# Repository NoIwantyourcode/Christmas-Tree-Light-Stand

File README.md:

# Christmas-Tree-Light-Stand
This a christmas tree light stand that I made as a part of hackclub blueprint
and yes to any reviewer wondering, I am aiming for that shiny new Bambu labs A1 mini

Below are some pictures of the PCB, Rendered PCB, case, Schematics and a fully assembled view

# Schematics

# PCB
The Christmas tree lightstand uses 2 PCBs, The Christmas tree shaped PCB contains all the LEDs and the smaller but also important pcb as it handles the timing of the flashing LEDs and power

# Rendered PCB

# Case

# fully assembled view

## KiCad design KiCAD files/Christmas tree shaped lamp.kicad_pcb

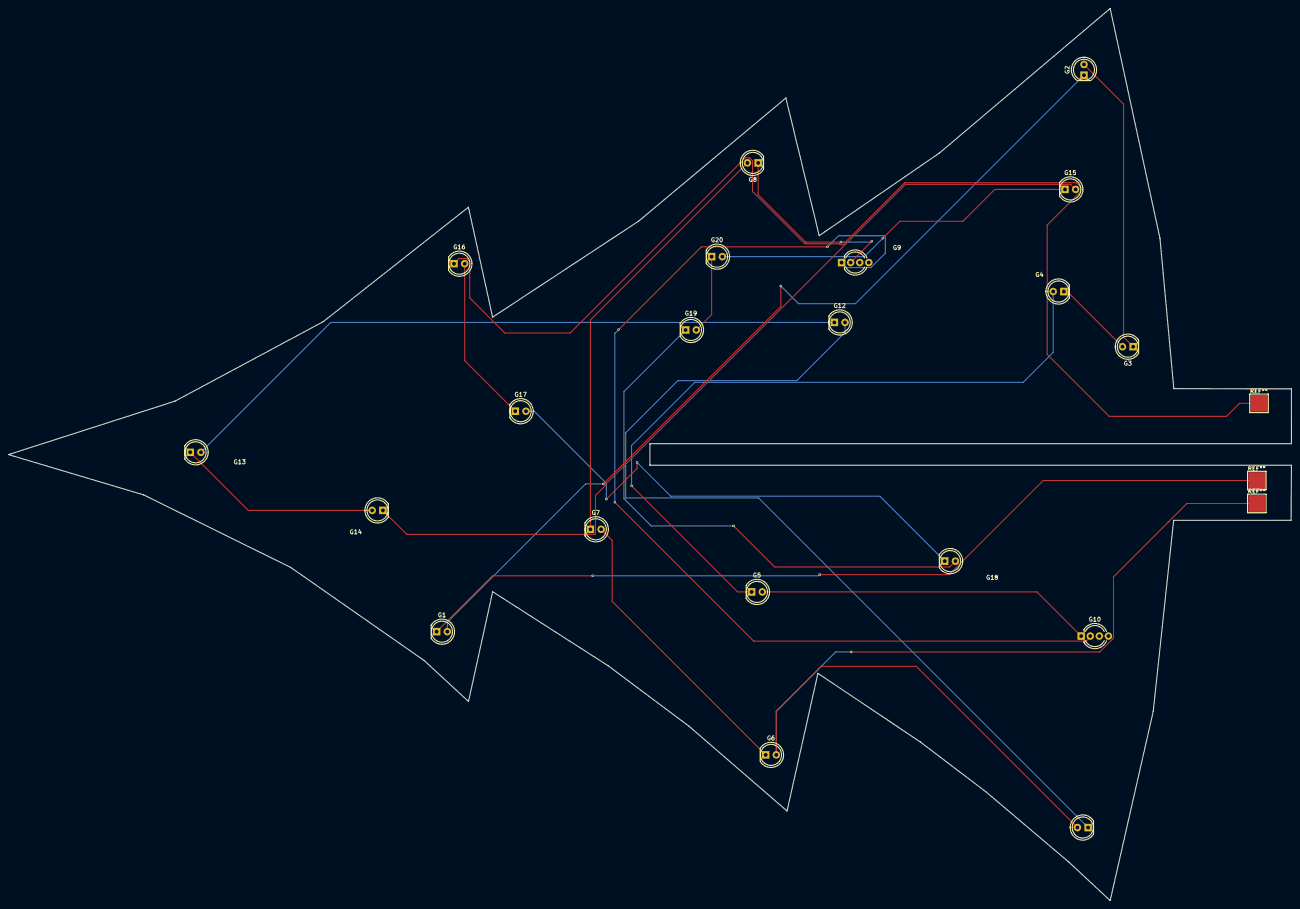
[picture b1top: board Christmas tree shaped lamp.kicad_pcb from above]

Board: 2 copper layers, 304.5 x 211.7 mm, 20 parts (0 on the bottom side), 19 nets.

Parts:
G1, G2, G3, G4, G5, G6, G7, G8, G11, G12, G13, G14, G15, G16, G17, G18, G19, G20: LED; LED_D5.0mm_Clear
G9, G10: LED; LED_D5.0mm-4_RGB_Wide_Pins

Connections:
unnamed: G1.2 (A), G2.1 (K)
unnamed: G2.2 (A), G3.1 (K)
unnamed: G3.2 (A), G4.1 (K)
unnamed: G4.2 (A), G5.1 (K)
unnamed: G6.1 (K), G7.2 (A)
unnamed: G7.1 (K), G8.2 (A)
unnamed: G8.1 (K), G9.2 (A)
unnamed: G9.1 (K), G10.2 (A)
unnamed: G5.2 (A), G10.1 (K)
unnamed: G6.2 (A), G11.2 (A)
unnamed: G11.1 (K), G12.2 (A)
unnamed: G12.1 (K), G13.2 (A)
unnamed: G13.1 (K), G14.2 (A)
unnamed: G14.1 (K), G15.2 (A)
unnamed: G15.1 (K), G20.2 (A)
unnamed: G16.2 (A), G17.1 (K)
unnamed: G17.2 (A), G18.1 (K)
unnamed: G18.2 (A), G19.1 (K)
unnamed: G19.2 (A), G20.1 (K)

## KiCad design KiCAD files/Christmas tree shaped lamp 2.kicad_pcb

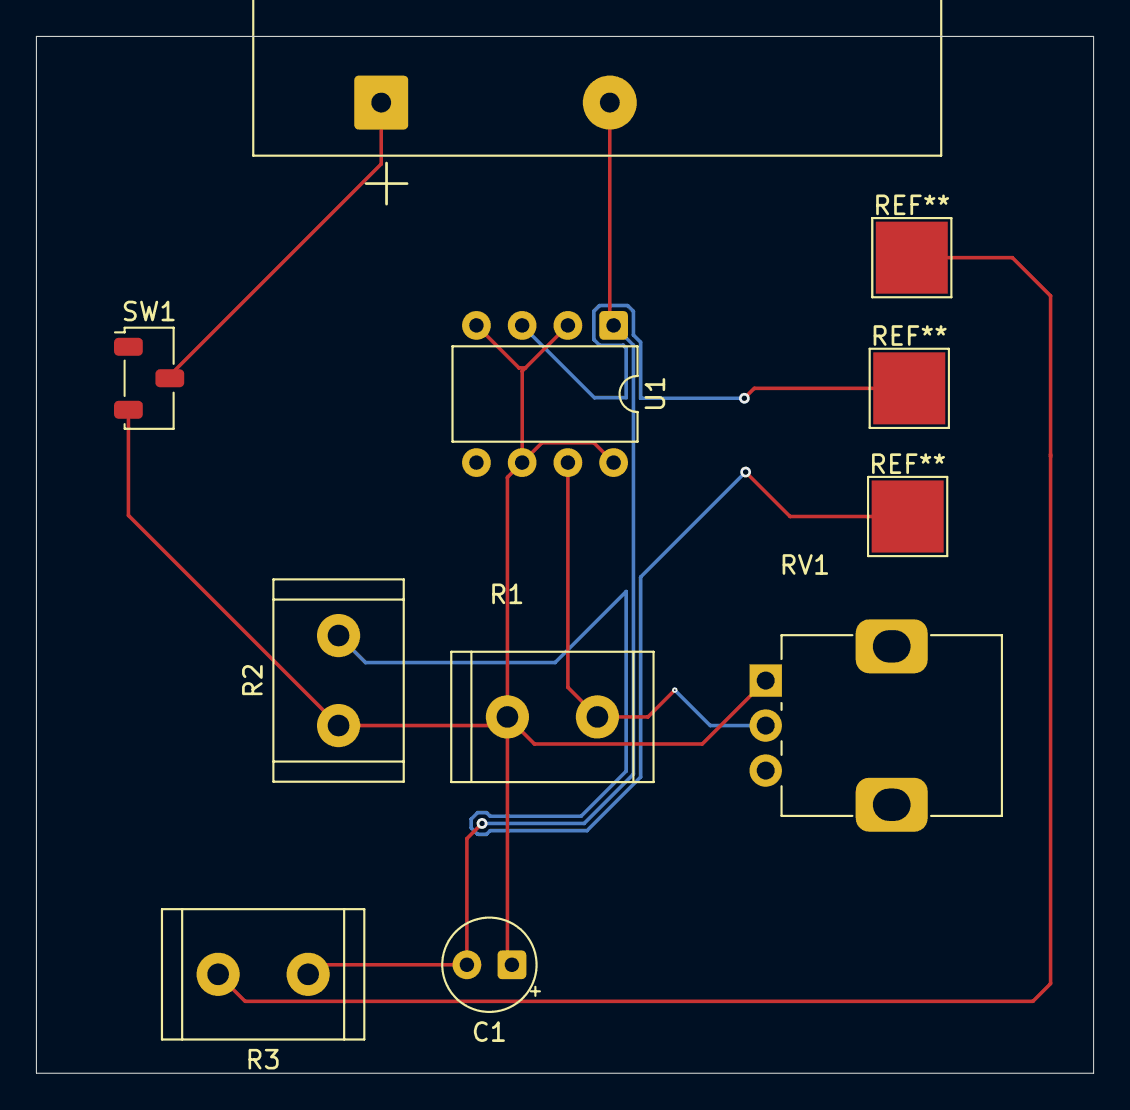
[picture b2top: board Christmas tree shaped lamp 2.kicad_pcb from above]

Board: 2 copper layers, 58.7 x 57.6 mm, 8 parts (0 on the bottom side), 4 nets.

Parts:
BT1: 9V; BatteryHolder_Keystone_2479_3xAAA
C1: 10uF; CP_Radial_Tantal_D5.0mm_P2.50mm
R1: 1K; R_Radial_Power_L11.0mm_W7.0mm_P5.00mm
R2, R3: 220R; R_Radial_Power_L11.0mm_W7.0mm_P5.00mm
RV1: R_Potentiometer_Trim_US; Potentiometer_Alps_RK09K_Single_Vertical
SW1: SW_Nidec_CAS-120A1; Nidec_Copal_CAS-120A
U1: LM555xN; DIP-8_W7.62mm

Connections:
unnamed: BT1.1 (+), SW1.2 (B)
unnamed: BT1.2 (-), C1.2, R3.1, U1.1 (GND)
unnamed: C1.1, R1.1, R2.1, RV1.1, SW1.3 (A), U1.2 (TR), U1.4 (R), U1.6 (THR), U1.8 (VCC)
unnamed: R1.2, RV1.2, U1.7 (DIS)

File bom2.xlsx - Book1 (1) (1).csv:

Components,Designators,Quantity,Links,Unit price,Final price
LEDS (Red),"G1, G2… G10",10,https://www.digikey.sg/en/products/detail/w%C3%BCrth-elektro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,0.21,2.1
LEDS (Green),"G11, G12… G20",10,https://www.digikey.sg/en/products/detail/marktech-optoelect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,0.238,2.38
Resistors (1Kohm),R1,1,https://www.digikey.sg/en/products/detail/stackpole-electron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,0.14,0.14
Resistors (220ohm),"R2, R3",2,https://www.digikey.sg/en/products/detail/stackpole-electron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,0.14,0.28
Battery (9V),BT1,1,https://www.digikey.sg/en/products/detail/panasonic-energy/6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,3.23,3.23
LM555N,U1,1,https://www.digikey.sg/en/products/detail/texas-instruments/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,1.67,1.67
Switch,SW1,1,https://www.digikey.sg/en/products/detail/e-switch/RA1113112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,0.99,0.99
9V Battery plug,BT1,1,https://www.digikey.sg/en/products/detail/keystone-electroni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,0.82,0.82
Potentiometer,,1,https://www.digikey.sg/en/products/detail/bourns-inc/3362P-1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,1.27,1.27
2-layer pcb,,2,-,2+4,6
 Capacitor (10uF),C1,10,https://www.lazada.sg/products/pdp-i1914780306-s10235809141.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,0.178,1.78
,,,,Total,19.66
,,,,Total+Shipping+GST,51.27
,,,,In USD,39.84

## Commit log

2026-01-01 Create del
2026-01-01 Added CAD files
2026-01-01 Added Schematics and PCB files
2026-01-02 Added Bill of Materials
2026-01-02 bom.csv
2026-01-02 Uploaded bom.csv
2026-01-02 added 1st pcb
2026-01-02 1st PCB upload
2026-01-02 added case files
2026-01-04 bom updated
2026-01-09 added updated bom
